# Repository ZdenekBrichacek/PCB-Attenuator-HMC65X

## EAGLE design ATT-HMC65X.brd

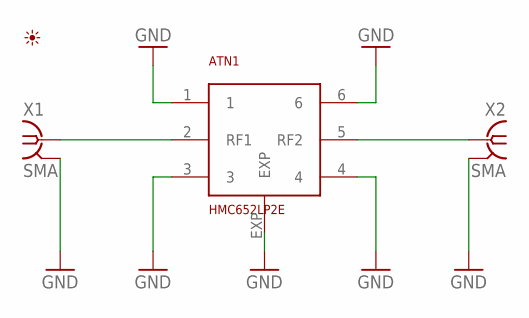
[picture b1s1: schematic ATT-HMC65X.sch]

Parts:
ATN1: HMC652LP2E; DFN-6_LP2
U$1: PICTO_1
X1, X2: SMA; J502-ND-142-0701-801/806

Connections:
GND: ATN1.1, ATN1.3, ATN1.4, ATN1.6, ATN1.EXP, X1.G@1 (2), X1.G@2 (2), X1.G@3 (2), X1.G@4 (2), X2.G@1 (2), X2.G@2 (2), X2.G@3 (2), X2.G@4 (2)
RF1: ATN1.2 (RF1), X1.1
RF2: ATN1.5 (RF2), X2.1

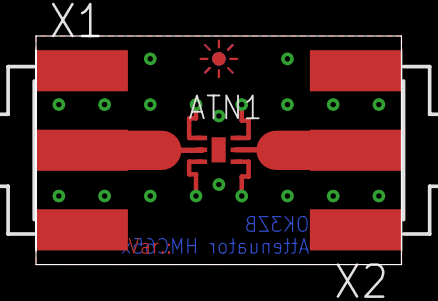
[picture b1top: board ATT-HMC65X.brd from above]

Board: 2 copper layers, 20.3 x 12.7 mm, 4 parts (0 on the bottom side), 3 nets.

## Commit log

2017-10-10 :neckbeard: Added .gitattributes & .gitignore files
2017-10-10 Initial version
